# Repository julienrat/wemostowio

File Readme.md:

Wemos to Wio node
=
 
----
##Principe
Ce tutoriel permet de convertir une carte Wemos en une carte compatible Wio Node. Et ainsi construire facilement des objets connectés.

###C'est quoi un Wio Node ?
Le Wio Node est une carte développée par Seeedstudio, basée sur un ESP8266 permettant de construire des petits appareils connectés à divers services tels que twitter, facebook, etc ...
La configuration du Wio Node se fait par un téléphone sous Android et via une application dédiée.

Pour plus d'informations, vous pouvez regarder la vidéo de présentation :

##Flasher le Wemos
### Récupérer le firmware Wio Node
[user1.bin](https://github.com/Seeed-Studio/Wio_Link/raw/master/users_build/local_user_00000000000000000000/user1.bin)

[user2.bin](https://github.com/Seeed-Studio/Wio_Link/raw/master/users_build/local_user_00000000000000000000/user2.bin)

[bootloader](http://www.seeedstudio.com/wiki/images/4/4b/Esp8266sdk1.4.1.zip)

Décompresser Bootloader et copier user1.bin, user2.bin, boot_v1.4(b1).bin, blank.bin et esp_init_data_default.bin dans le même repertoire
### Installer esptool 
Suivant votre distribution, vous pouvez trouver esptool dans vos dépots, ou le télécharger à cette adresse https://github.com/themadinventor/esptool

### Flasher le Wemos Sous Linux

```shell
esptool -p /dev/ttyUSB0 -b 230400 write_flash --flash_size 32m-c1 0x0000 boot_v1.4\(b1\).bin 0x1000 user1.bin 0x101000 user2.bin 0x3fc000 esp_init_data_default.bin 0x3fe000 blank.bin

```
### Flasher le Wemos Sous Windows
Il vous faudra un utilitaire de flashage pour Windows disponibla à cette adresse : (http://bbs.espressif.com/download/file.php?id=856)

Puis configurez le logiciel comme ci-dessous

## Installer l'application Android
https://play.google.com/store/apps/details?id=cc.seeed.iot.ap

## Utilisation // Configuration
###Configuration
- Appuyer sur le bouton fonction 4 secondes afin de mettre le wemos en mode "Configuration". La led arrete de clignoter et effectue un "fading".
- Démarrer l'application Wio sur le téléphone.

Description | Screenshot
---------|---------
Connectez vous ou créez un compte |  
Ajoutez votre Wemos, et choisissez Wio Node |  
Assurez-vous que la led bleue effectue un "fading", sinon appuyez 4 sec sur le bouton Fonction | 
Connectez vous au wemos, il devrait apparaitre dans la liste | 
Choisissez un nom pour votre Wemos | 
Choisissez le capteur que vous souhaitez connecter au wemos | 
A l'aide d'un drag'n'drop glissez le capteur sur un connecteur de votre choix | 
Cliquez sur "Update Firmware" pour envoyer la nouvelle configuration au wemos | 

Voilà, votre wemos est opérationel, il ne reste plus qu'à le connecter à un canal de diffusion, ici c'est le canal de diffusion IFTTT que nous alons choisir.

###Utilisation simple
Pour l'instant Un seul canal est disponible pour wio : IFTTT 

Ce service, apres inscription permet de relier nos capteurs à une multitude de services tels que Twitter, Facebook et même les lamps connectées de chez philips .. etc.

Le principe est simple IF This Then That.(Si Ceci Alors Cela) et se présente sous la forme de recettes : Le site [IFTTT](https://ifttt.com)

Par exemple :
Un tweet quand il fait chaud :

On peux aussi connecter IFTTT à la platteforme IO d'adafruit

[Recette IFTTT](https://ifttt.com/recipes/452996-temperature-data-viz)| [DashBoard Adafruit](https://io.adafruit.com/ratjulien/welcome-dashboard)
---------|---------
 |  

###Schéma de câblage
[Fritzing](/schema/wemos_wio_sch.fzz)| Eagle
---------|---------
 |  

###Vue PCB
Top | Bottom 
---------|---------
 |  

###Production
Typon | [Plaque d'essais](/schema/wemos_wio_plaque_essais.fzz)
---------|---------
 |  

##Sources
Ce projet est sous licence CCbySA

Ressources seeedstudio : 
- https://github.com/Seeed-Studio/Wio_Link/wiki/Advanced%20User%20Guide
- https://github.com/Seeed-Studio/Wio_Link

Ressources Wemos
- http://www.wemos.cc/

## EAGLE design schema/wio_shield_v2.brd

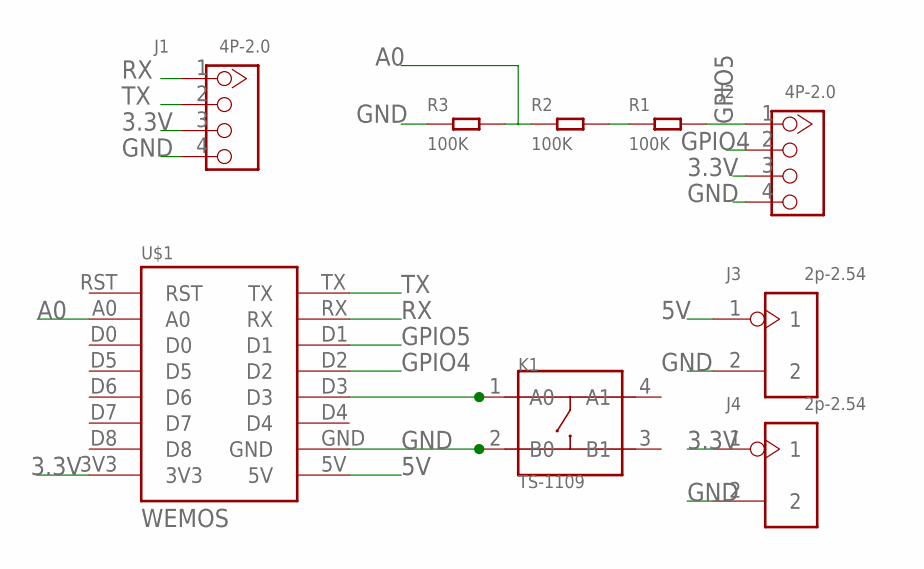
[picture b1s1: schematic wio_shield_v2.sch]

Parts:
J1, J2: 4P-2.0; HW4-2.0
J3, J4: 2p-2.54; H2-2.54
K1: TS-1109; SW4-6.0X6.0X5.0MM
R1, R2, R3: 100K; PR-D1.8*L3.3MM
U$1: WEMOS

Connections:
3.3V: J1.3, J2.3, J4.1, U$1.3V3
5V: J3.1, U$1.5V
A0: R2.6 (1), R3.5 (2), U$1.A0
GND: J1.4, J2.4, J3.2, J4.2, K1.2 (B0), R3.6 (1), U$1.GND
GPIO4: J2.2, U$1.D2
GPIO5: J2.1, R1.5 (2), U$1.D1
unnamed: R1.6 (1), R2.5 (2)
unnamed: K1.1 (A0), U$1.D3
RX: J1.1, U$1.RX
TX: J1.2, U$1.TX

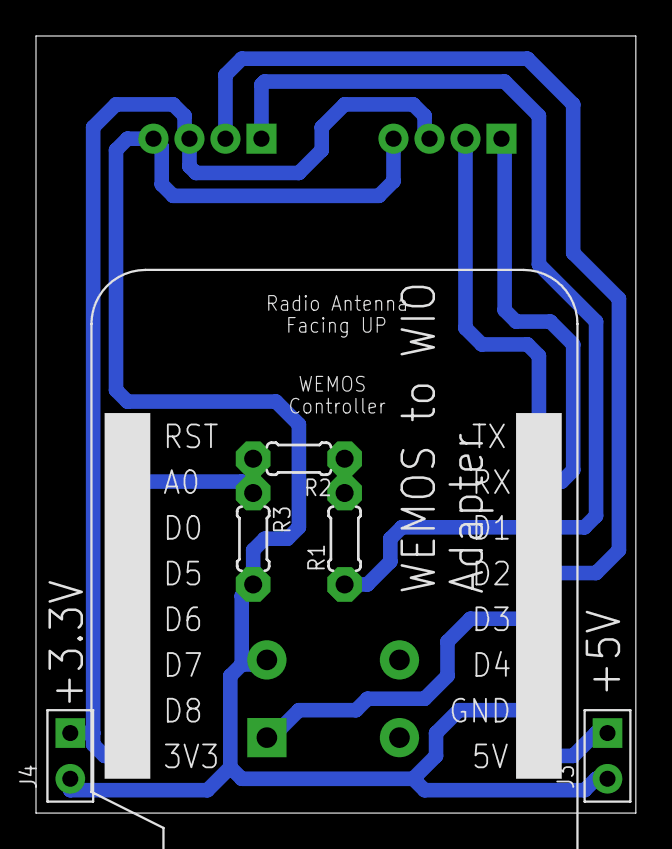
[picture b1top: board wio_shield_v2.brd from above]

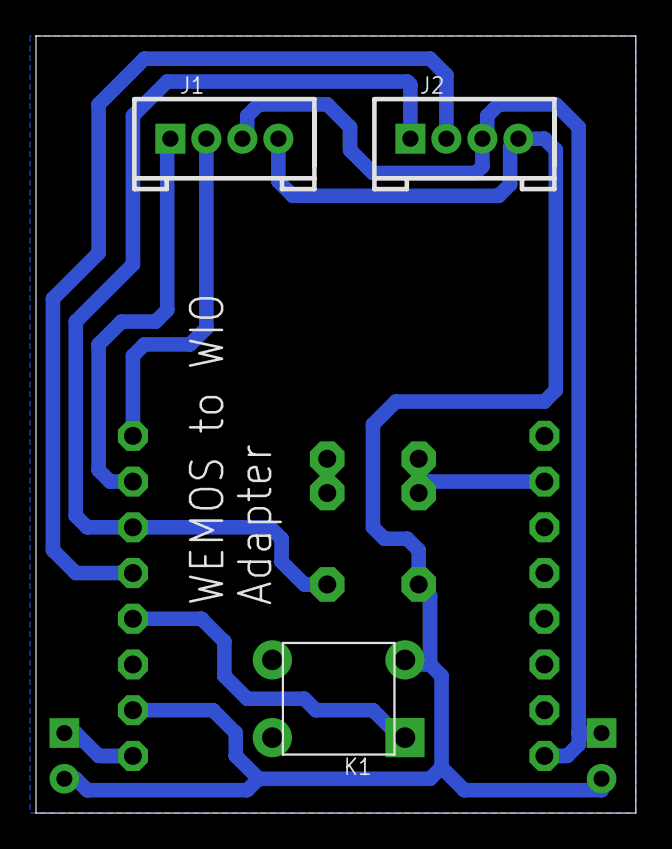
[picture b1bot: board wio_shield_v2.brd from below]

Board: 2 copper layers, 33.3 x 43.2 mm, 9 parts (3 on the bottom side), 10 nets.

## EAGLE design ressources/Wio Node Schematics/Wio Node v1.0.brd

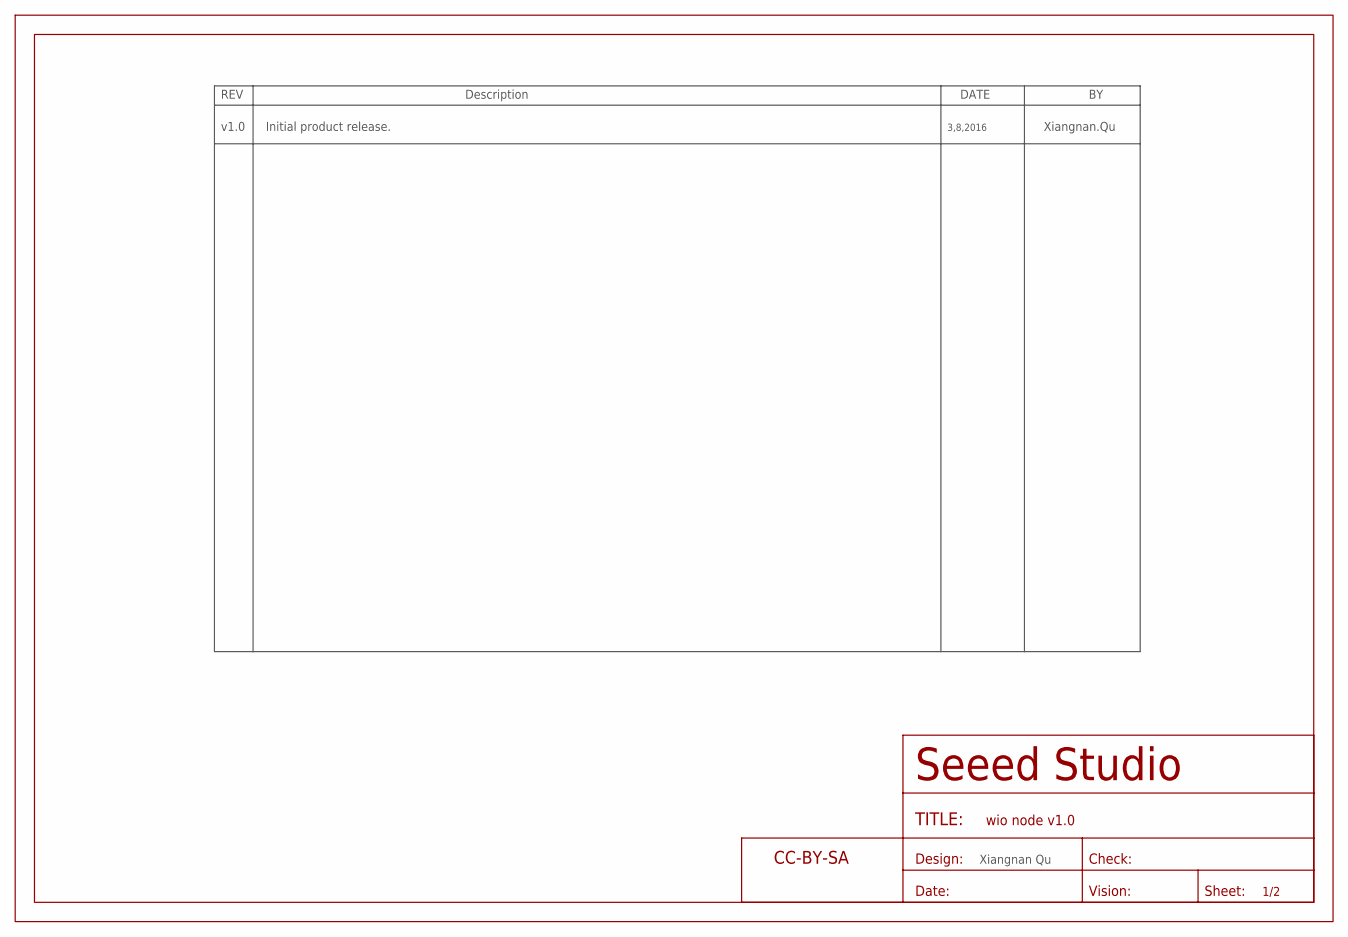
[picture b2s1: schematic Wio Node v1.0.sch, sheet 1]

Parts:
FR4: SEEEDSTUDIO-OPEN-SCH-FRAME; SEEEDSTUDIO-PCB-FRAME

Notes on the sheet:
v1.0
Initial product release.
3,8,2016
Xiangnan.Qu
Xiangnan Qu

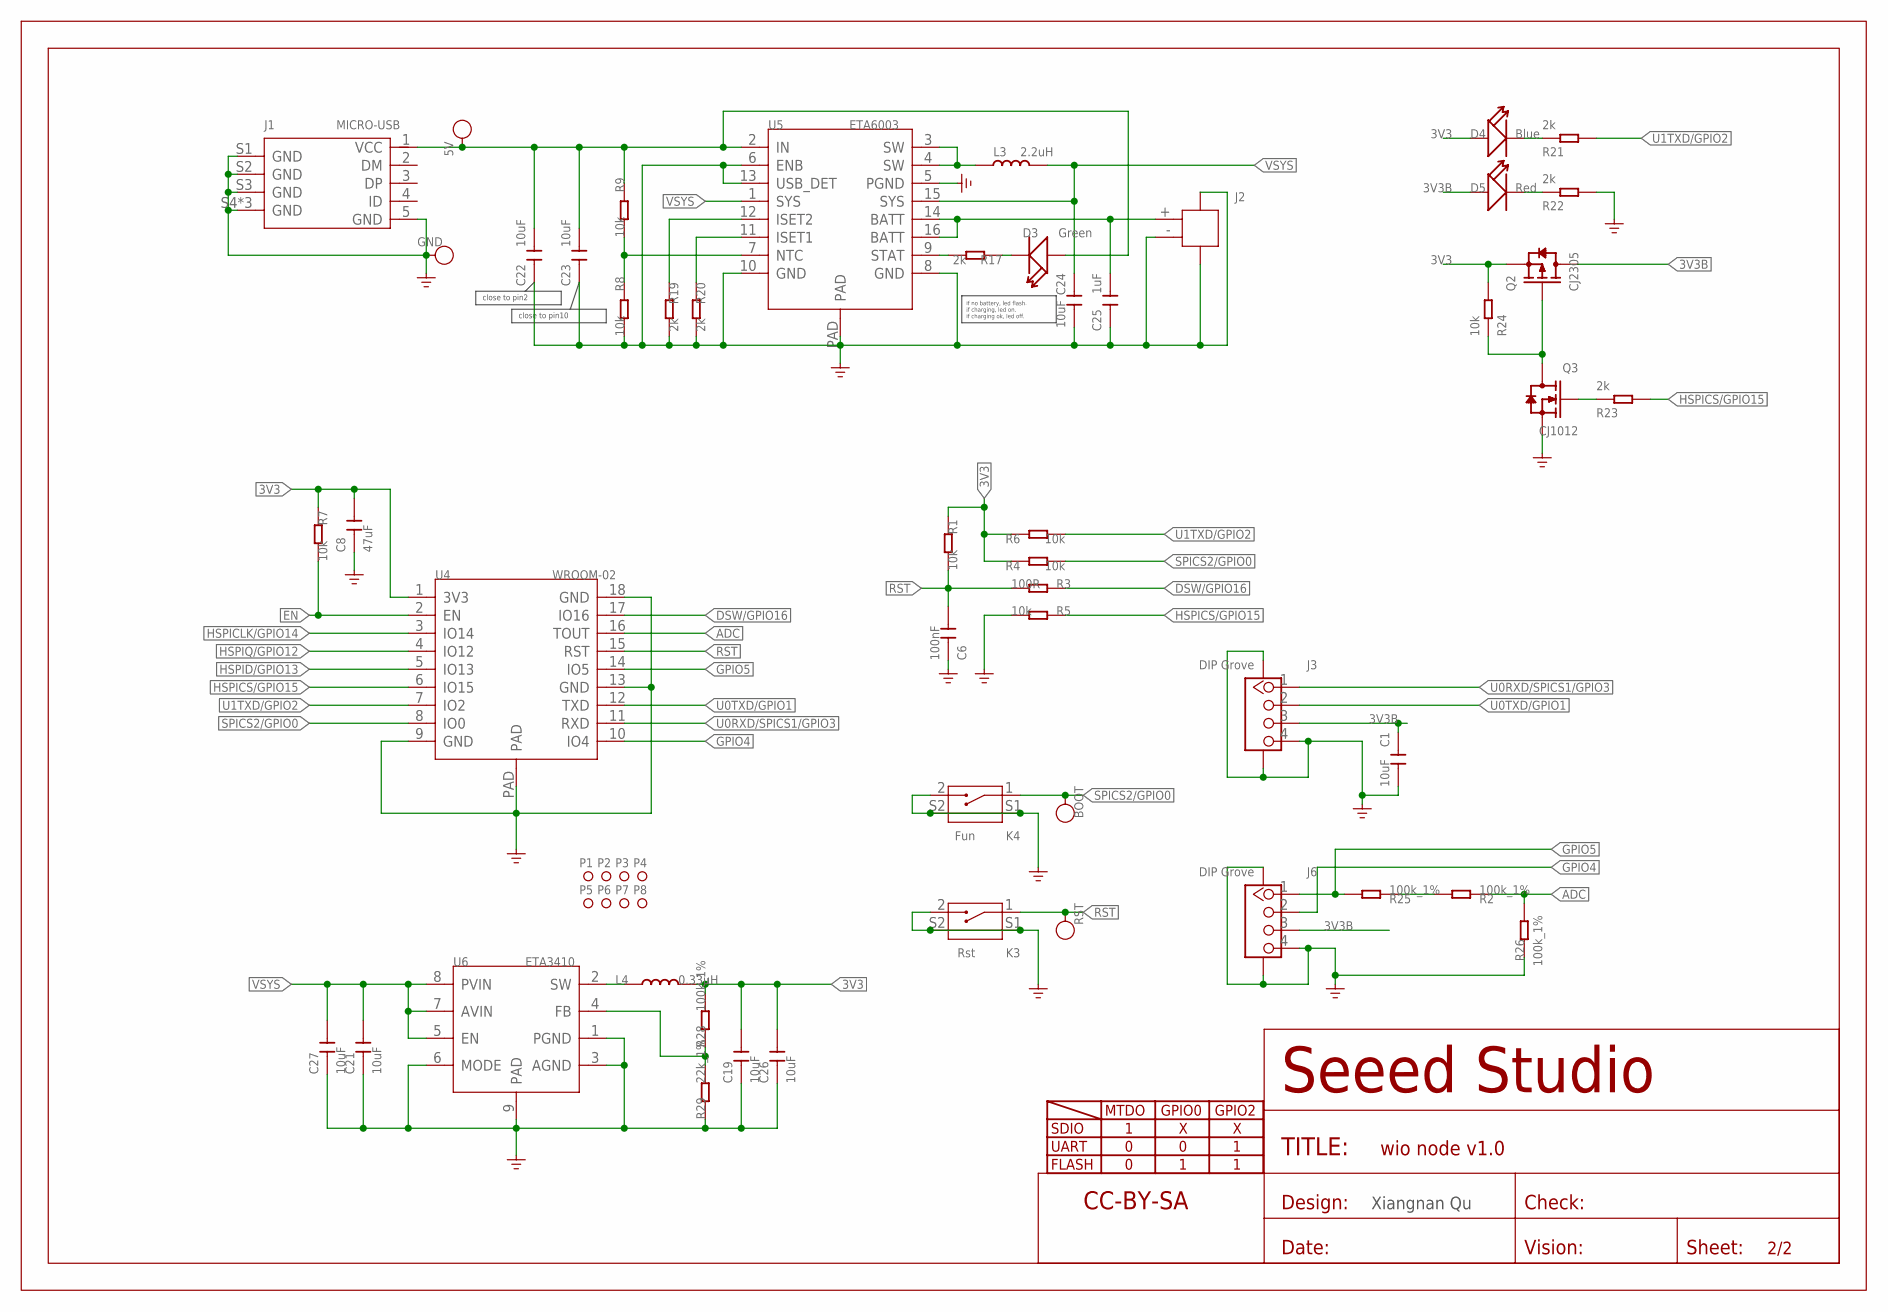
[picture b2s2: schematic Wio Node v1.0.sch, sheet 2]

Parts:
5V: TEST-POINT'4545'; TP-D45MIL
BOOT: TEST-POINT'4545'; TP-D45MIL
C1, C19, C21, C23, C24, C26, C27: 10uF; C0402
C6: 100nF; C0201
C8: 47uF; C0805
C22: 10uF; C0805
C25: 1uF; C0402
D3: Green; LED-0402
D4: Blue; LED-0402
D5: Red; LED-0402
FR1: SEEEDSTUDIO-OPEN-SCH-FRAME; SEEEDSTUDIO-PCB-FRAME
GND: TEST-POINT'4545'; TP-D45MIL
J1: MICRO-USB; MICRO-USB5+4P-SMD-0.65-B
J2: JST-2P-SMD'2.0'; HW2-SMD-2.0-90D
J3, J6: DIP Grove; HW4-SMD-2.0-90D
K3: Rst; SW4-SMD-4.5X3.8X1.8MM-90D
K4: Fun; SW4-SMD-4.5X3.8X1.8MM-90D
L3: 2.2uH; L0805
L4: 0.33uH; L201610
P1, P2, P3, P4, P5, P6, P7, P8: MARK-1.0'ANNULAR'; ROUND-MARK-1.0
Q2: CJ2305; SOT-23
Q3: CJ1012; SOT-523
R1, R4, R5, R6, R7, R8, R9, R24: 10k; R0201
R2, R25, R26, R28: 100k_1%; R0201
R3: 100R; R0201
R17, R19, R20, R21, R22, R23: 2k; R0201
R29: 22k_1%; R0402
RST: TEST-POINT'4545'; TP-D45MIL
U4: WROOM-02; ESP18-SMD-1.5-18X20MM
U5: ETA6003; QFN16G-0.5-3X3MM
U6: ETA3410; DFN8G-0.5-2X2MM

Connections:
3V3: C8.2, C19.2, C26.2, D4.+, L4.2, Q2.2 (S), R1.1, R4.1, R6.1, R7.1, R24.2, R28.2, U4.1 (3V3)
3V3B: C1.1, D5.+, J3.3, J6.3, Q2.3 (D)
ADC: R2.1, R26.2, U4.16 (TOUT)
DSW/GPIO16: R3.1, U4.17 (IO16)
EN: R7.2, U4.2 (EN)
GND: C1.2, C6.1, C8.1, C19.1, C21.1, C22.2, C23.2, C24.2, C25.2, C26.1, C27.1, GND.T, J1.5 (GND), J1.S1 (GND), J1.S2 (GND), J1.S3 (GND), J1.S4 (GND), J1.S5 (GND), J1.S6 (GND), J2.3, J2.4, J2.- (2), J3.4, J3.SS1, J3.SS2, J6.4, J6.SS1, J6.SS2, K3.2, K3.S1, K3.S2, K4.2, K4.S1, K4.S2, Q3.2 (S), R5.2, R8.2, R19.2, R20.2, R22.2, R26.1, R29.1, U4.9 (GND), U4.13 (GND), U4.18 (GND), U4.PAD, U5.5 (PGND), U5.6 (ENB), U5.8 (GND), U5.10 (GND), U5.13 (USB_DET), U5.PAD, U6.1 (PGND), U6.3 (AGND), U6.6 (MODE), U6.9 (PAD)
GPIO4: J6.2, U4.10 (IO4)
GPIO5: J6.1, R25.2, U4.14 (IO5)
HSPICLK/GPIO14: U4.3 (IO14)
HSPICS/GPIO15: R5.1, R23.2, U4.6 (IO15)
HSPID/GPIO13: U4.5 (IO13)
HSPIQ/GPIO12: U4.4 (IO12)
unnamed: R2.2, R25.1
unnamed: R8.1, R9.2, U5.7 (NTC)
unnamed: Q2.1 (G), Q3.3 (D), R24.1
unnamed: Q3.1 (G), R23.1
unnamed: D4.-, R21.1
unnamed: D5.-, R22.1
unnamed: L3.1, U5.3 (SW), U5.4 (SW)
unnamed: C25.1, J2.+ (1), U5.14 (BATT), U5.16 (BATT)
unnamed: L4.1, U6.2 (SW)
unnamed: D3.-, R17.1
unnamed: R17.2, U5.9 (STAT)
unnamed: R28.1, R29.2, U6.4 (FB)
unnamed: R20.1, U5.11 (ISET1)
unnamed: R19.1, U5.12 (ISET2)
RST: C6.2, K3.1, R1.2, R3.2, RST.T, U4.15 (RST)
SPICS2/GPIO0: BOOT.T, K4.1, R4.2, U4.8 (IO0)
U0RXD/SPICS1/GPIO3: J3.1, U4.11 (RXD)
U0TXD/GPIO1: J3.2, U4.12 (TXD)
U1TXD/GPIO2: R6.2, R21.2, U4.7 (IO2)
VSYS: C21.2, C24.1, C27.2, L3.2, U5.1 (SYS), U5.15 (SYS), U6.5 (EN), U6.7 (AVIN), U6.8 (PVIN)
VUSB: 5V.T, C22.1, C23.1, D3.+, J1.1 (VCC), R9.1, U5.2 (IN)

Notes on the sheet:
SDIO
UART
FLASH
MTDO
GPIO0
GPIO2
Xiangnan Qu
close to pin10
if no battery, led flash. if charging, led on. if charging ok, led off.
close to pin2

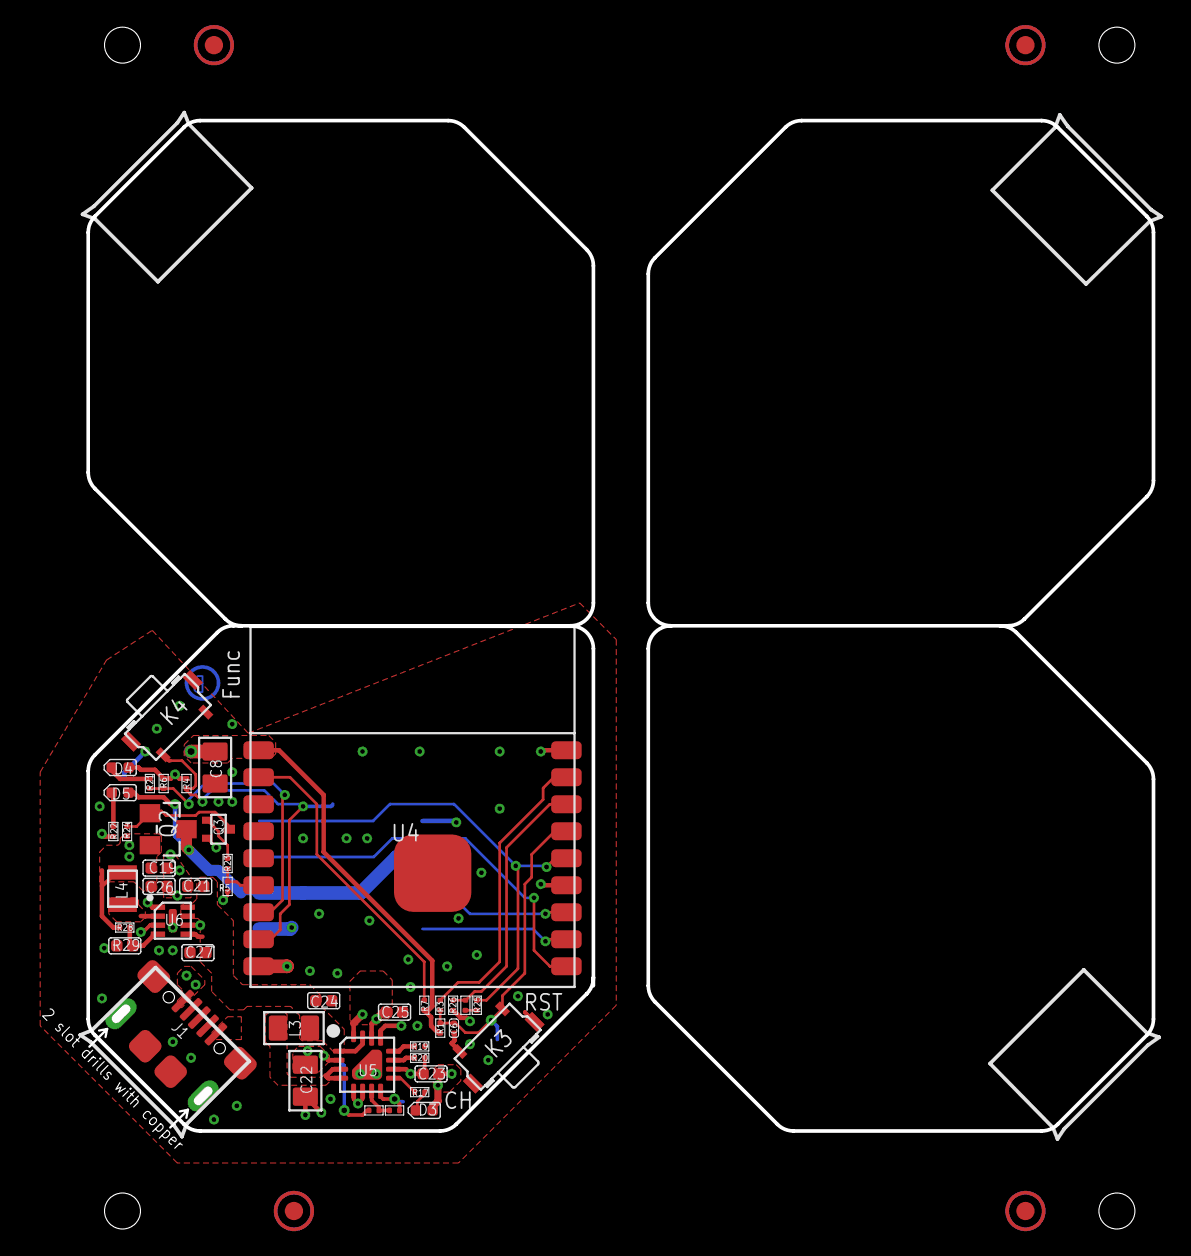
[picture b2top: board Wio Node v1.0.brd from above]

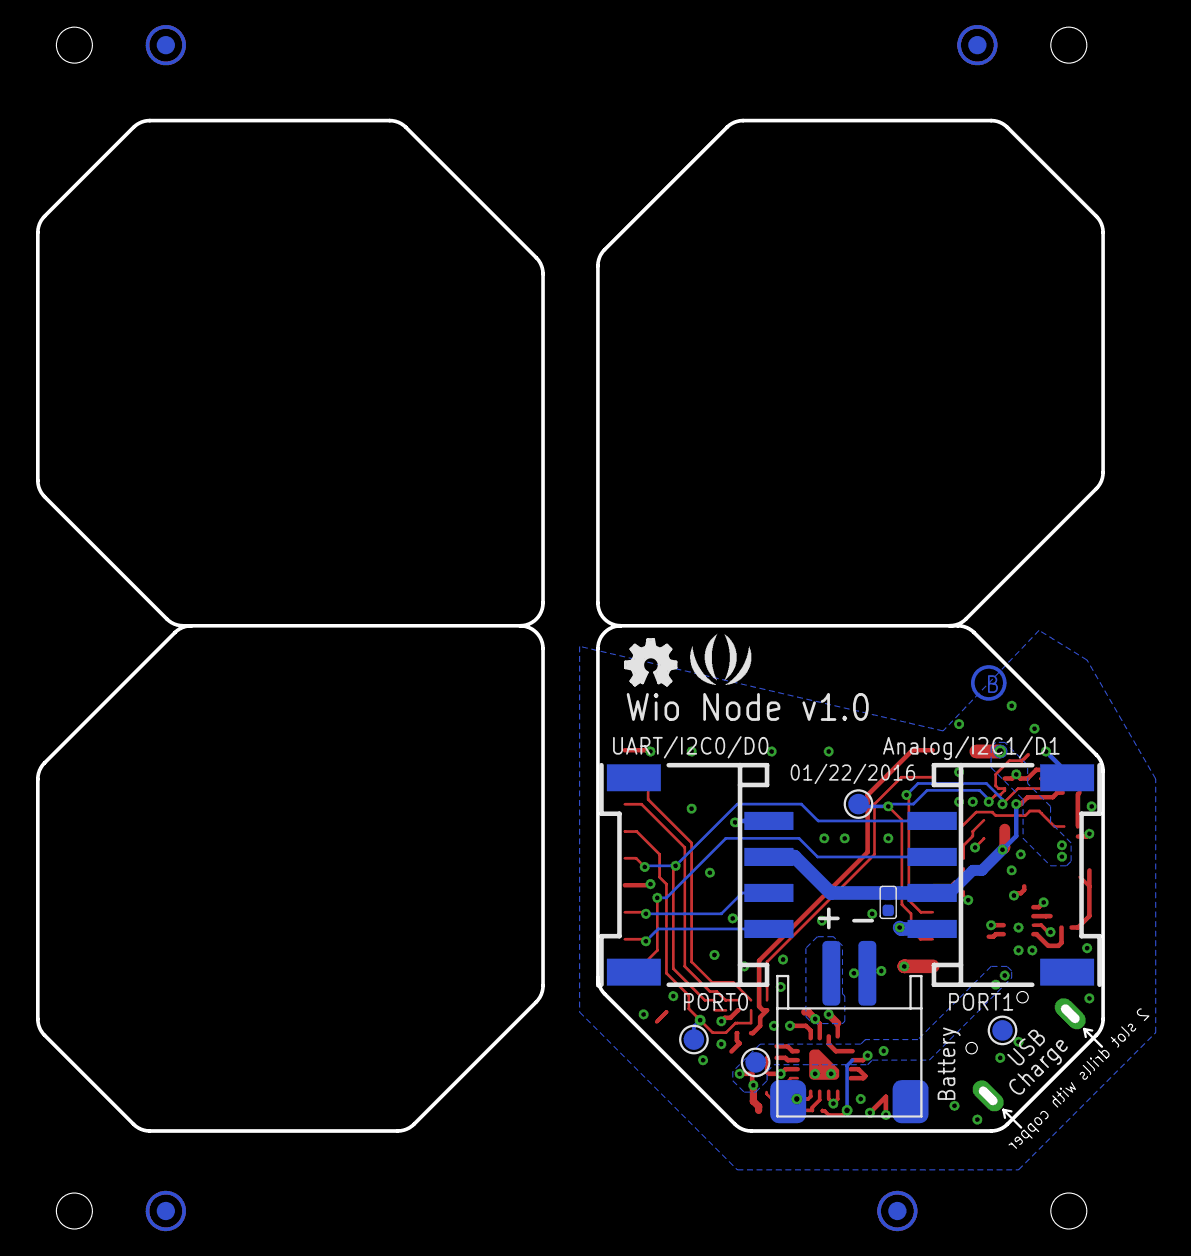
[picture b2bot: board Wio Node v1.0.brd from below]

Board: 2 copper layers, 28.1 x 56.1 mm, 63 parts (14 on the bottom side), 30 nets.

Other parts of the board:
U$2: OSHW_FILLX100_NOTEXT
U$3: SEEED-SILK-160*153MIL

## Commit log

2016-08-10 + ‘.sparkleshare’ + ‘SparkleShare.txt’
2016-08-10 + ‘3D/’ + ‘3D/wio_shield.png’ + ‘3D/wio_shield.pov’ + ‘3D/wio_shield.pov.none.txt’ + ‘3D/wio_shield.sh’ + ‘3D/wio_shield_top.png’ + ‘eagle.epf’ + ‘ressources/Wio Node Schematics/Wio Node v1.0.brd’ + 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
2016-08-10 / ‘3D/wio_shield_top.png’
2016-08-10 / ‘3D/wio_shield.png’
2016-08-11 - ‘3D/wio_shield.pov.none.txt’
2016-08-11 - ‘3D/wio_shield.pov’ - ‘3D/wio_shield.sh’
2016-08-11 - ‘eagle.epf’ - ‘wio_shield.b##’ - ‘wio_shield.b#1’ - ‘wio_shield.b#2’ - ‘wio_shield.s#1’ - ‘wio_shield.s#2’ - ‘wio_shield.s#3’
2016-08-11 + ‘Schema/’
2016-08-11 < ‘Schema/’ > ‘schema/’
2016-08-11 < ‘wio_shield.brd’ > ‘schema/wio_shield.brd’ < ‘wio_shield.sch’ > ‘schema/wio_shield.sch’ - ‘wio_shield.mpd’
2016-08-11 + ‘Readme.md’
2016-08-11 / ‘Readme.md’
2016-08-11 + ‘images/’
2016-08-11 + ‘images/video.png’
2016-08-11 + ‘images/WioNode_plaque_essais.png’
2016-08-11 + ‘images/WioNode_sch.png’
2016-08-11 / ‘images/WioNode_plaque_essais.png’
2016-08-11 + ‘schema/.wio_shield.brd.lck’ + ‘schema/.wio_shield.sch.lck’ + ‘schema/wio_shield.b#1’ / ‘schema/wio_shield.brd’ + ‘schema/wio_shield.s#1’ / ‘schema/wio_shield.sch’
2016-08-11 + ‘images/PCB.png’
2016-08-11 + ‘images/WioNode_sch_fritzing.png’
2016-08-11 + ‘schema/wemos_wio_sch.fzz’
2016-08-11 + ‘schema/wemos_wio_plaque_essais.fzz’
2016-08-11 / ‘schema/wemos_wio_sch.fzz’
2016-08-11 / ‘images/WioNode_sch_fritzing.png’
2016-08-11 - ‘schema/.wio_shield.brd.lck’ - ‘schema/.wio_shield.sch.lck’
2016-08-11 - ‘schema/wio_shield.b#1’ - ‘schema/wio_shield.s#1’
2016-08-11 + ‘images/add_device.png’ + ‘images/device_name.png’ + ‘images/login.png’ + ‘images/next.png’ + ‘images/reseau_device.png’ + ‘images/reseau_local.png’ + ‘images/sensor_choose.png’ + ‘images/sensor_ch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
2016-08-11 / ‘images/upload.png’
2016-08-11 / ‘images/sensor_choose2.png’
2016-08-11 / ‘images/sensor_choose.png’
2016-08-11 / ‘images/reseau_local.png’
2016-08-11 / ‘images/reseau_device.png’
2016-08-11 / ‘images/next.png’
2016-08-11 / ‘images/login.png’
2016-08-11 / ‘images/device_name.png’
2016-08-11 / ‘images/add_device.png’
2016-08-11 + ‘images/recette.png’
2016-08-11 + ‘images/recette_adafruit.png’
2016-08-11 + ‘images/recette_ada.png’
2016-08-18 + ‘schema/BOM.csv’
2016-08-18 / ‘schema/BOM.csv’
2016-08-18 + ‘images/config_esp.jpeg’
2016-08-19 + ‘3D/wio_shield_v2.png’ + ‘3D/wio_shield_v2top.png’
2016-08-19 + ‘schema/wio_shield_v2.brd’ + ‘schema/wio_shield_v2.sch’
2016-08-19 / ‘3D/wio_shield_v2.png’
2016-08-19 / ‘3D/wio_shield_v2top.png’
2016-08-19 + ‘images/WioNode_sch_v2.png’
2016-08-19 / ‘images/WioNode_sch_v2.png’
2016-08-19 < ‘images/WioNode_sch_v2.png’ > ‘images/PCB_v2.png’
2016-08-19 / ‘images/PCB_v2.png’

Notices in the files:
parts and their libraries:
moudle-new: This work is licensed under the Creative Commons Attribution 4.0 International License.
To view a copy of this license,visit:
http://creativecommons.org/licenses/by-sa/4.0
